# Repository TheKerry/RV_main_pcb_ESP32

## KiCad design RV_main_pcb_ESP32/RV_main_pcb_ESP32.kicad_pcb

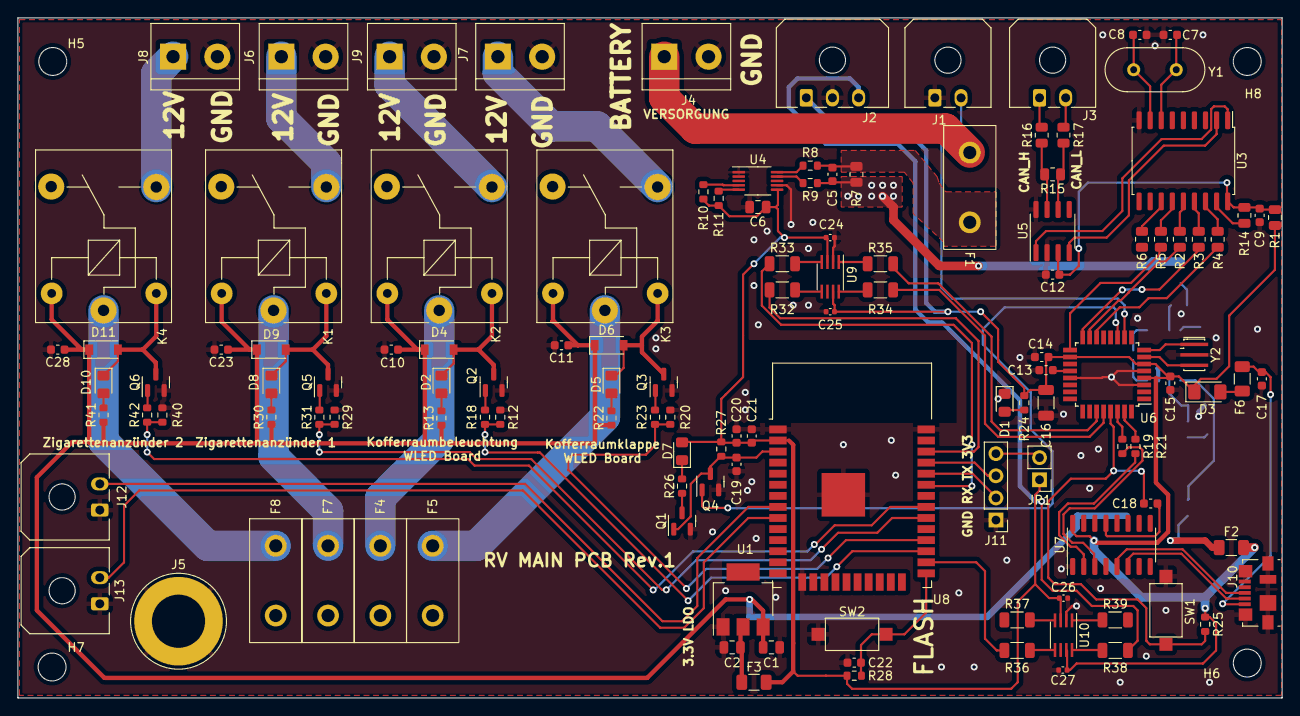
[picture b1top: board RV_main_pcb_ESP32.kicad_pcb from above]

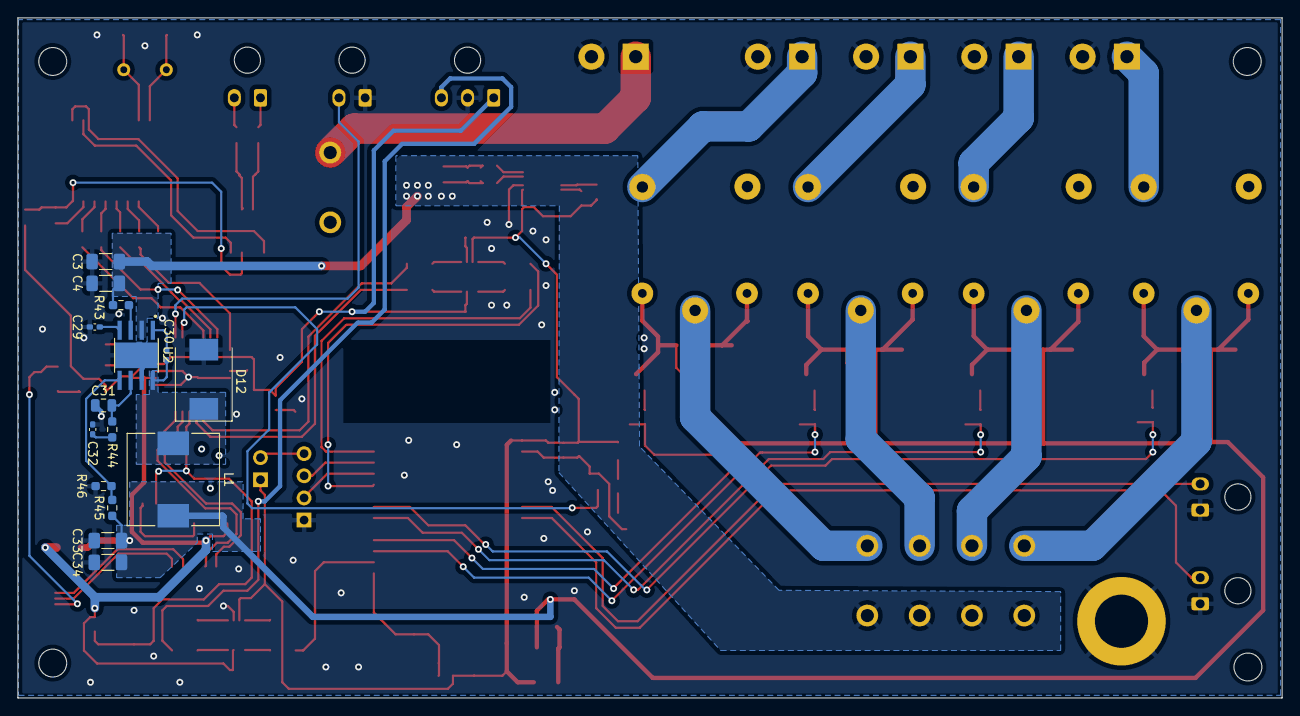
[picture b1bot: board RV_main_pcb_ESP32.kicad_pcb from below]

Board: 2 copper layers, 145.0 x 78.0 mm, 143 parts (15 on the bottom side), 101 nets.

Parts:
C1, C2, C6: 0.1uF; C_0805_2012Metric
C3, C4: 10uF; C_1206_3216Metric_Pad1.33x1.80mm_HandSolder
C5, C19, C22: 0.1uF; C_0603_1608Metric
C7, C8, C9, C12: C; C_0603_1608Metric
C10, C11, C23, C28: 10uF; C_0603_1608Metric
C13, C14, C15, C17, C18, C20: 100nF; C_0603_1608Metric
C16: 4,7uF 16V; C_1206_3216Metric
C21: 22uF; C_0603_1608Metric
C24, C25, C26, C27: 100nF; C_0402_1005Metric
C29: 22uF; C_0402_1005Metric_Pad0.74x0.62mm_HandSolder
C30, C32: 100nF; C_0402_1005Metric_Pad0.74x0.62mm_HandSolder
C31: 10pF; C_0805_2012Metric
C33, C34: 47uF; C_1206_3216Metric_Pad1.33x1.80mm_HandSolder
D1, D7: GREEN; LED_0805_2012Metric_Pad1.15x1.40mm_HandSolder
D2, D5, D8, D10: LED; LED_0805_2012Metric_Pad1.15x1.40mm_HandSolder
D3: D_Filled; D_1206_3216Metric_Pad1.42x1.75mm_HandSolder
D4, D6, D9, D11: 1N4148W; D_SOD-123
D12: B340; D_SMC
F1, F4, F5, F7, F8: 10A; Flachsicherung
F2, F6: 0.5A; Fuse_1206_3216Metric
F3: 1A; Fuse_1206_3216Metric
H5, H6, H7, H8: MountingHole; MountingHole_3.2mm_M3
J1, J3, J12, J13: Conn_01x02_Male; Molex_Micro-Fit_3.0_43650-0200_1x02_P3.00mm_Horizontal
J2: Molex Micro-fit 3x1; Molex_Micro-Fit_3.0_43650-0300_1x03_P3.00mm_Horizontal
J4, J6, J7, J8, J9: Conn_01x02_Male; TerminalBlock_bornier-2_P5.08mm
J5: Conn_01x01_Female; Banana_Jack_1Pin
J10: USB_B_Micro; USB_Micro-B_Molex_47346-0001
J11: Conn_01x04_Male; PinHeader_1x04_P2.54mm_Vertical
JP1: Jumper_2_Open; PinHeader_1x02_P2.54mm_Vertical
K1, K2, K3, K4: SANYOU_SRD_Form_C; Relay_SPDT_SANYOU_SRD_Series_Form_C
L1: 6.8uH; L_10.4x10.4_H4.8
Q1, Q2, Q3, Q4, Q5, Q6: AO3400A; SOT-23
R1, R2, R3, R4, R5, R6, R16, R17: 0; R_0805_2012Metric
R7: 0.01; R_0805_2012Metric
R8, R9: 10; R_0603_1608Metric
R10, R11: 4,7k; R_0603_1608Metric
R12, R20, R25, R27, R28, R29, R40: 10k; R_0603_1608Metric
R13, R22, R30, R41: R; R_0603_1608Metric
R14: 10k; R_0805_2012Metric
R15: 120; R_0805_2012Metric
R18, R23, R31, R42: 100; R_0603_1608Metric
R19, R21: 1k; R_0603_1608Metric
R24: 250; R_0603_1608Metric
R26: 125; R_0603_1608Metric
R32, R33, R34, R35, R36, R37, R38, R39: 0; R_1206_3216Metric
R43: 0; R_0603_1608Metric_Pad0.98x0.95mm_HandSolder
R44: 61.9k; R_0603_1608Metric_Pad0.98x0.95mm_HandSolder
R45: 10.2k; R_0603_1608Metric_Pad0.98x0.95mm_HandSolder
R46: 1.96k; R_0603_1608Metric_Pad0.98x0.95mm_HandSolder
SW1, SW2: SW_Push; SW_SPST_CK_RS282G05A3
U1: LM1117-5; SOT-223
U2: TPS54331DDAR; CONV_TPS54331DDAR
U3: MCP2515-xSO; SOIC-18W_7.5x11.6mm_P1.27mm
U4: INA226; VSSOP-10_3x3mm_P0.5mm
U5: TJA1051T; SOIC-8_3.9x4.9mm_P1.27mm
U6: ATmega328P-A; TQFP-32_7x7mm_P0.8mm
U7: CH340C; SOIC-16_3.9x9.9mm_P1.27mm
U8: ESP32-WROOM-32
U9, U10: TXS0102DCT; SSOP-8_2.95x2.8mm_P0.65mm
Y1: Crystal; Crystal_HC49-4H_Vertical
Y2: Crystal_GND2; Resonator_SMD_Murata_CSTxExxV-3Pin_3.0x1.1mm_HandSoldering

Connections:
+5V: C1.1, C10.1, C11.1, C23.1, C28.1, C33.1, C34.1, D4.1 (K), D6.1 (K), D9.1 (K), D11.1 (K), F2.1, K1.5, K2.5, K3.5, K4.5, L1.2, R13.1, R22.1, R30.1, R41.1, R45.2, U1.3 (VI)
+12V: C3.1, C4.1, C5.1, F4.2, F5.2, F7.2, F8.2, R7.1, R9.2, R43.1, U2.2 (VIN)
/5V 3A Buck/TPS_PH: C30.2, D12.1 (K), L1.1, U2.8 (PH)
/CAN Interface/CAN_H: J3.1, R16.2
/CAN Interface/CAN_L: J3.2, R17.2
/CAN Interface/VCC: C9.1, C12.1, R1.2, R14.2, U3.18 (VDD), U5.3 (VCC)
/ESP32/ESP_RX: J11.2, U8.34 (RXD0/IO3)
/ESP32/ESP_TX: J11.3, U8.35 (TXD0/IO1)
/LM1117 fixed voltage1/VOUT: C2.2, F3.1, U1.2 (VO)
/Relay 10A1/NO: J7.1, K3.3
/Relay 10A2/NO: J6.1, K1.3
/Relay 10A3/NO: J8.1, K4.3
/Relay 10A/NO: J9.1, K2.3
BATTERY: C5.2, F1.2, R7.2, R8.1
CAN_CS: R4.1, U6.14 (PB2)
CAN_MISO: R3.1, U6.16 (PB4)
CAN_MOSI: R2.1, U6.15 (PB3)
CAN_RX: U3.2 (RXCAN), U5.4 (RXD)
CAN_SCK: R5.1, U6.17 (PB5)
CAN_TX: U3.1 (TXCAN), U5.1 (TXD)
ESP32_EN_INT: C19.1, Q1.1 (G), Q4.3 (D), R27.1, U8.3 (EN)
ESP32_RELAY_1: R12.1, R18.1, U8.27 (IO16)
ESP32_RELAY_2: R20.1, R23.1, U8.28 (IO17)
ESP32_RELAY_3: R29.1, R31.1, U8.30 (IO18)
ESP32_RELAY_4: R40.1, R42.1, U8.31 (IO19)
ESP32_VCC: C6.1, C20.1, C21.1, C24.2, C26.2, D7.2 (A), F3.2, JP1.1 (A), R10.2, R11.1, R27.2, R28.2, U4.6 (VS), U8.2 (VDD), U9.3 (VCCA), U10.3 (VCCA)
ESP32_WS2812B_status_LED_3.3V: R36.1, U8.26 (IO4)
ESP32_WS2812B_status_LED_5V: J2.3, R38.2
ESP-32_SCL_3.3V: R32.1, U8.36 (IO22)
ESP-32_SDA_3.3V: R33.1, U8.33 (IO21)
ESP_SW1: J12.2, U8.8 (IO32)
ESP_SW2: J13.2, U8.9 (IO33)
GND: C1.2, C2.1, C3.2, C4.2, C6.2, C7.1, C8.1, C9.2, C10.2, C11.2, C12.2, C13.1, C14.2, C15.2, C16.2, C17.1, C19.2, C20.2, C21.2, C22.2, C23.2, C24.1, C25.2, C26.1, C27.2, C28.2, C29.1, C31.1, C32.1, C33.2, C34.2, D1.1 (K), D12.2 (A), J1.1, J2.2, J4.2, J5.1, J6.2, J7.2, J8.2, J9.2, J10.5 (GND), J10.6 (Shield), J11.1, J12.1, J13.1, Q1.2 (S), Q2.2 (S), Q3.2 (S), Q4.2 (S), Q5.2 (S), Q6.2 (S), R12.2, R20.2, R29.2, R40.2, R46.1, SW1.1, SW2.1, U1.1 (GND), U2.7 (GND), U2.9 (POWERPAD), U3.9 (VSS), U4.1 (A1), U4.2 (A0), U4.7 (GND), U5.2 (GND), U5.8 (S), U6.3 (GND), U6.5 (GND), U6.21 (GND), U7.1 (GND), U8.1 (GND), U8.15 (GND), U8.38 (GND), U8.39 (GND), U9.2 (GND), U10.2 (GND), Y2.2
NANO_5V: C14.1, C15.1, C16.1, C25.1, C27.1, D3.1 (K), F2.2, J2.1, R1.1, R24.1, R25.2, U6.4 (VCC), U6.6 (VCC), U6.18 (AVCC), U7.16 (VCC), U9.7 (VCCB), U10.7 (VCCB)
NANO_D6: J1.2, U6.10 (PD6)
NANO_D7: Q4.1 (G), U6.11 (PD7)
NANO_RESET: C18.2, R25.1, SW1.2, U6.29 (~RESET/PC6)
NANO_RX: R19.2, U7.3 (RXD)
NANO_SCL_5V: R34.2, U6.28 (PC5)
NANO_SDA_5V: R35.2, U6.27 (PC4)
NANO_TX: R21.2, U7.2 (TXD)
unnamed: C7.2, U3.7 (OSC2), Y1.2
unnamed: C8.2, U3.8 (OSC1), Y1.1
unnamed: C13.2, U6.20 (AREF)
unnamed: C17.2, F6.1, J10.1 (VBUS)
unnamed: C18.1, U7.13 (~DTR)
unnamed: C22.1, R28.1, SW2.2, U8.25 (IO0)
unnamed: C29.2, U2.4 (SS)
unnamed: C30.1, U2.1 (BOOT)
unnamed: C31.2, R44.1, U2.6 (COMP)
unnamed: C32.2, R44.2
unnamed: D1.2 (A), R24.2
unnamed: D2.1 (K), D4.2 (A), K2.2, Q2.3 (D)
unnamed: D2.2 (A), R13.2
unnamed: D3.2 (A), F6.2
unnamed: D5.1 (K), D6.2 (A), K3.2, Q3.3 (D)
unnamed: D5.2 (A), R22.2
unnamed: D7.1 (K), R26.2
unnamed: D8.1 (K), D9.2 (A), K1.2, Q5.3 (D)
unnamed: D8.2 (A), R30.2
unnamed: D10.1 (K), D11.2 (A), K4.2, Q6.3 (D)
unnamed: D10.2 (A), R41.2
unnamed: F1.1, J4.1
unnamed: F4.1, K2.1
unnamed: F5.1, K3.1
unnamed: F7.1, K1.1
unnamed: F8.1, K4.1
unnamed: J10.2 (D-), U7.6 (UD-)
unnamed: J10.3 (D+), U7.5 (UD+)
unnamed: J11.4, JP1.2 (B)
unnamed: Q1.3 (D), R26.1
unnamed: Q2.1 (G), R18.2
unnamed: Q3.1 (G), R23.2
unnamed: Q5.1 (G), R31.2
unnamed: Q6.1 (G), R42.2
unnamed: R2.2, U3.14 (SI)
unnamed: R3.2, U3.15 (SO)
unnamed: R4.2, U3.16 (~CS)
unnamed: R5.2, U3.13 (SCK)
unnamed: R6.1, U3.12 (~INT)
unnamed: R8.2, U4.10 (Vin+)
unnamed: R9.1, U4.9 (Vin-)
unnamed: R14.1, U3.17 (~RESET)
unnamed: R15.1, R17.1, U5.6 (CANL)
unnamed: R15.2, R16.1, U5.7 (CANH)
unnamed: R19.1, U6.30 (PD0)
unnamed: R21.1, U6.31 (PD1)
unnamed: R32.2, U9.5 (A1)
unnamed: R33.2, U9.4 (A2)
unnamed: R34.1, U9.8 (B1)
unnamed: R35.1, U9.1 (B2)
unnamed: R36.2, U10.5 (A1)
unnamed: R37.2, U10.4 (A2)
unnamed: R38.1, U10.8 (B1)
unnamed: R39.1, U10.1 (B2)
unnamed: R43.2, U2.3 (EN)
unnamed: U6.7 (XTAL1/PB6), Y2.3
unnamed: U6.8 (XTAL2/PB7), Y2.1
SCK: R11.2, U4.5 (SCL)
SD: R10.1, U4.4 (SDA)
TPS_VSENSE: R45.1, R46.2, U2.5 (VSENSE)

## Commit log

2022-02-02 Version 1 verworfen
2022-02-08 drawio inserted
2022-02-08 drawio
2022-02-12 drawio update
2022-03-02 schematics
2022-03-02 Hardware
2022-03-11 downgrade
2022-05-21 assembly V1
2022-05-26 Software initial upload
2022-07-19 update CAN Frames
2022-07-29 updated V2 Software excluded CAN
2022-07-31 updated V2 Software
